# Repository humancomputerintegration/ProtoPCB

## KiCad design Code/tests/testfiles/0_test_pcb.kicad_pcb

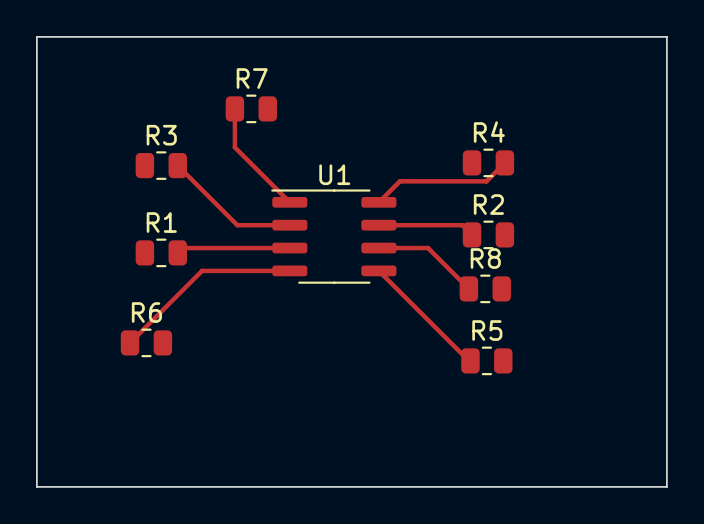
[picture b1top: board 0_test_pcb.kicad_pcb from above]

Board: 2 copper layers, 35.0 x 25.0 mm, 9 parts (0 on the bottom side), 8 nets.

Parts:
R1, R2, R3, R4, R5, R6, R7, R8: R; R_0805_2012Metric
U1: LMC555xM; SOIC-8_3.9x4.9mm_P1.27mm

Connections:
unnamed: R5.1, U1.5 (CV)
unnamed: R2.1, U1.7 (DIS)
unnamed: R7.1, U1.1 (GND)
unnamed: R1.2, U1.3 (Q)
unnamed: R6.1, U1.4 (R)
unnamed: R8.1, U1.6 (THR)
unnamed: R3.2, U1.2 (TR)
unnamed: R4.2, U1.8 (VCC)

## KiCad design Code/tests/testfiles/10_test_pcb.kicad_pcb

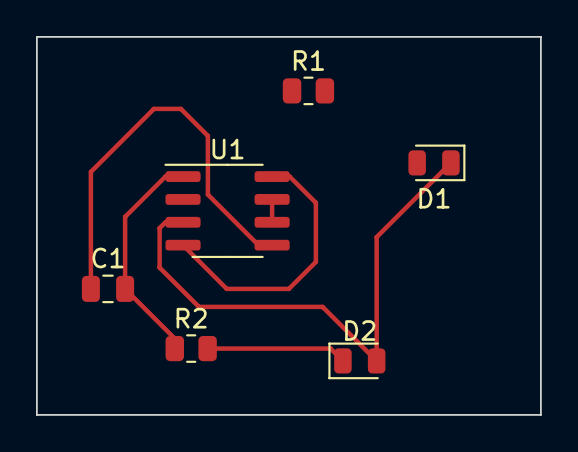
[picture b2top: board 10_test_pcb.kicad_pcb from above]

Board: 2 copper layers, 28.0 x 21.0 mm, 6 parts (0 on the bottom side), 7 nets.

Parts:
C1: C; C_0805_2012Metric
D1, D2: LED; LED_0805_2012Metric
R1, R2: R; R_0805_2012Metric
U1: LM555xM; SOIC-8_3.9x4.9mm_P1.27mm

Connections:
GND: C1.2, R2.1, U1.1 (GND)
unnamed: D1.2 (A), R1.1
unnamed: D1.1 (K), D2.2 (A), U1.3 (Q)
unnamed: D2.1 (K), R2.2
unnamed: C1.1, U1.5 (CV)
unnamed: U1.6 (THR), U1.7 (DIS)
VCC: R1.2, U1.4 (R), U1.8 (VCC)
